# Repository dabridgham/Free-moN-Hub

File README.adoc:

= Free-monN Hub

This is a simple circuit board that acts as a wiring hub for a
Free-moN module or section.  It basically just replaces (some of) the
terminal strips that one might use on a simple module and adds a 12
VDC linear regulator, a reversing relay, and LEDs to indicate power on
the ACC and DCC busses.

See the https://github.com/dabridgham/Free-moN-Hub/wiki[wiki] for more
information.

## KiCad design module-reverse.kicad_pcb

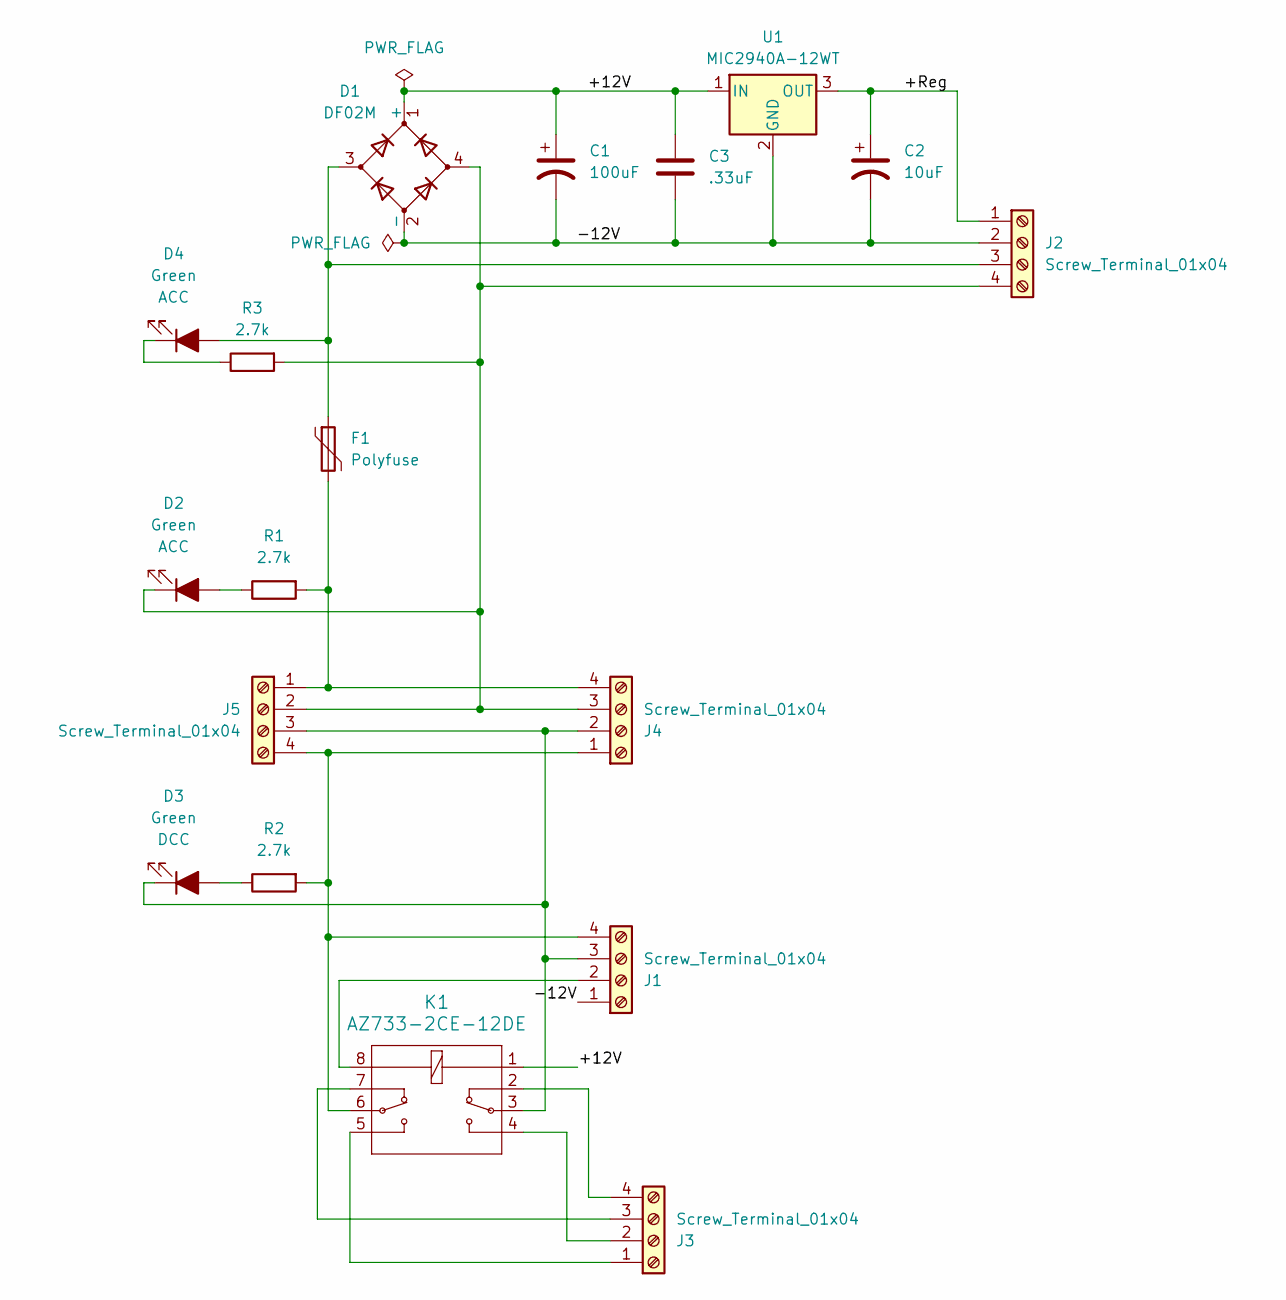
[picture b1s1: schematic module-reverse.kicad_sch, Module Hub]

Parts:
C1: 100uF; CP_Radial_D8.0mm_P3.50mm; MPN 50YXJ100MT78X11.5
C2: 10uF; CP_Radial_Tantal_D5.5mm_P5.00mm; MPN TAP106K025CRS
C3: .33uF; C_Disc_D5.0mm_W2.5mm_P5.00mm; MPN FA24X7R1H334KNU06
D1: DF02M; Diode_Bridge_DIP-4_W7.62mm_P5.08mm; MPN DF02M
D2, D3, D4: Green; LED_D3.0mm; MPN 151031VS06000
F1: Polyfuse; Fuse_Bourns_MF-RG300; MPN MF-R020
J1, J2, J3, J4, J5: Screw_Terminal_01x04; CUI_TB005-762-04BE; MPN TB005-762-04BE
K1: AZ733-2CE-12DE; AZ733-2C_AMZ; MPN AZ733-2CE-12DE
R1, R2, R3: 2.7k; R_Axial_DIN0207_L6.3mm_D2.5mm_P10.16mm_Horizontal; MPN CFR-25JB-52-2K7
U1: MIC2940A-12WT; TO-220-3_Vertical; MPN MIC2940A-12WT

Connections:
/+12V: C1.1, C3.1, D1.1 (+), K1.1, U1.1 (IN)
/+Reg: C2.1, J2.1, U1.3 (OUT)
/-12V: C1.2, C2.2, C3.2, D1.2 (-), J1.1, J2.2, U1.2 (GND)
unnamed: D2.2 (A), R1.1
unnamed: D1.4, D2.1 (K), J2.4, J4.3, J5.2, R3.2
unnamed: D3.2 (A), R2.1
unnamed: D3.1 (K), J1.3, J4.2, J5.3, K1.3
unnamed: D1.3, D4.2 (A), F1.1, J2.3
unnamed: D4.1 (K), R3.1
unnamed: J1.2, K1.8
unnamed: J1.4, J4.1, J5.4, K1.6, R2.2
unnamed: J3.1, K1.5
unnamed: J3.2, K1.4
unnamed: J3.3, K1.7
unnamed: J3.4, K1.2
unnamed: F1.2, J4.4, J5.1, R1.2

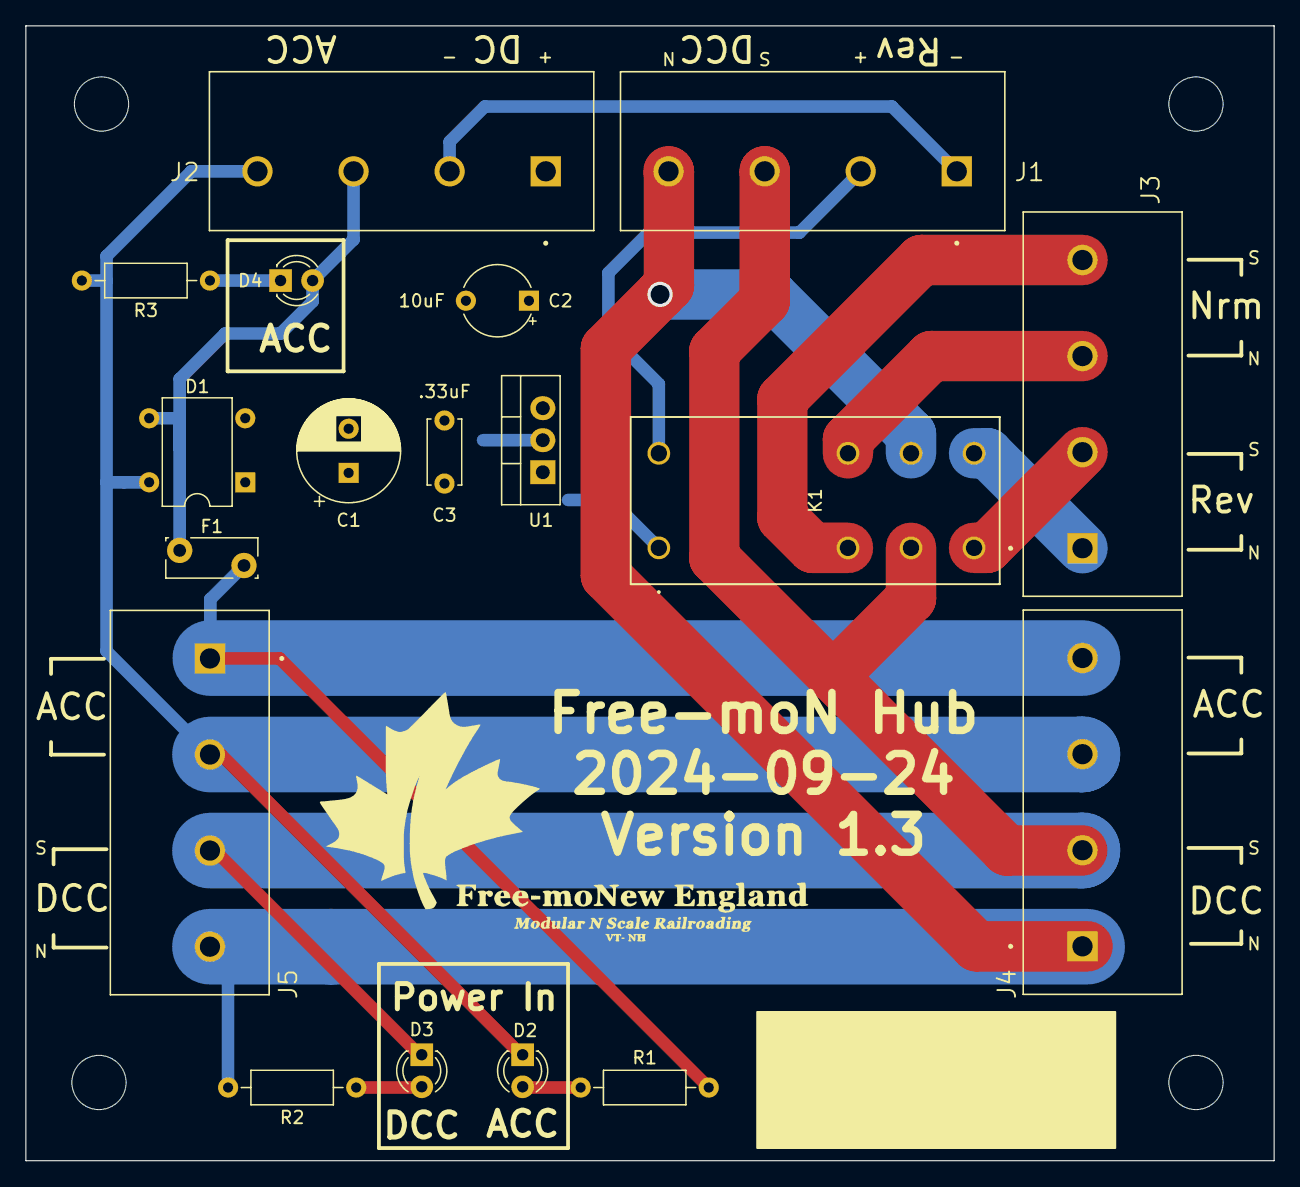
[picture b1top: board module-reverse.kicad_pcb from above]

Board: 2 copper layers, 99.0 x 90.0 mm, 18 parts (0 on the bottom side), 16 nets.

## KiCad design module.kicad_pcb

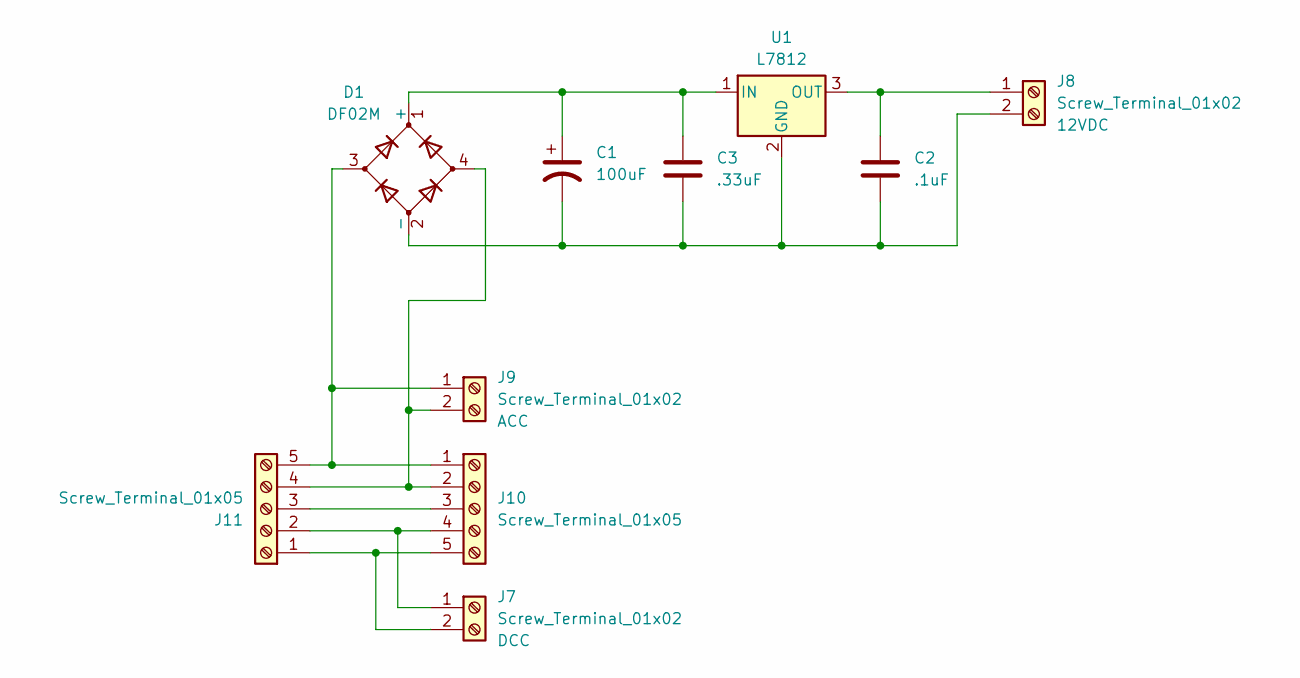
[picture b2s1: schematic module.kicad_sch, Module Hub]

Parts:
C1: 100uF; CP_Radial_D8.0mm_P3.50mm; MPN 50YXJ100MT78X11.5
C2: .1uF; C_Disc_D5.0mm_W2.5mm_P5.00mm; MPN FA28X7R1H104KNU00
C3: .33uF; C_Disc_D5.0mm_W2.5mm_P5.00mm; MPN FA24X7R1H334KNU06
D1: DF02M; Diode_Bridge_DIP-4_W7.62mm_P5.08mm; MPN DF02M
J7, J8, J9: Screw_Terminal_01x02; CUI_TB005-762-02BE; MPN TB005-762-02BE
J10, J11: Screw_Terminal_01x05; CUI_TB005-762-05BE; MPN TB005-762-05BE
U1: L7812; TO-220-3_Vertical; MPN L7812CV

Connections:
unnamed: C1.1, C3.1, D1.1 (+), U1.1 (IN)
unnamed: C1.2, C2.2, C3.2, D1.2 (-), J8.2, U1.2 (GND)
unnamed: C2.1, J8.1, U1.3 (OUT)
unnamed: D1.3, J9.1, J10.1, J11.5
unnamed: D1.4, J9.2, J10.2, J11.4
unnamed: J10.3, J11.3
unnamed: J7.1, J10.4, J11.2
unnamed: J7.2, J10.5, J11.1

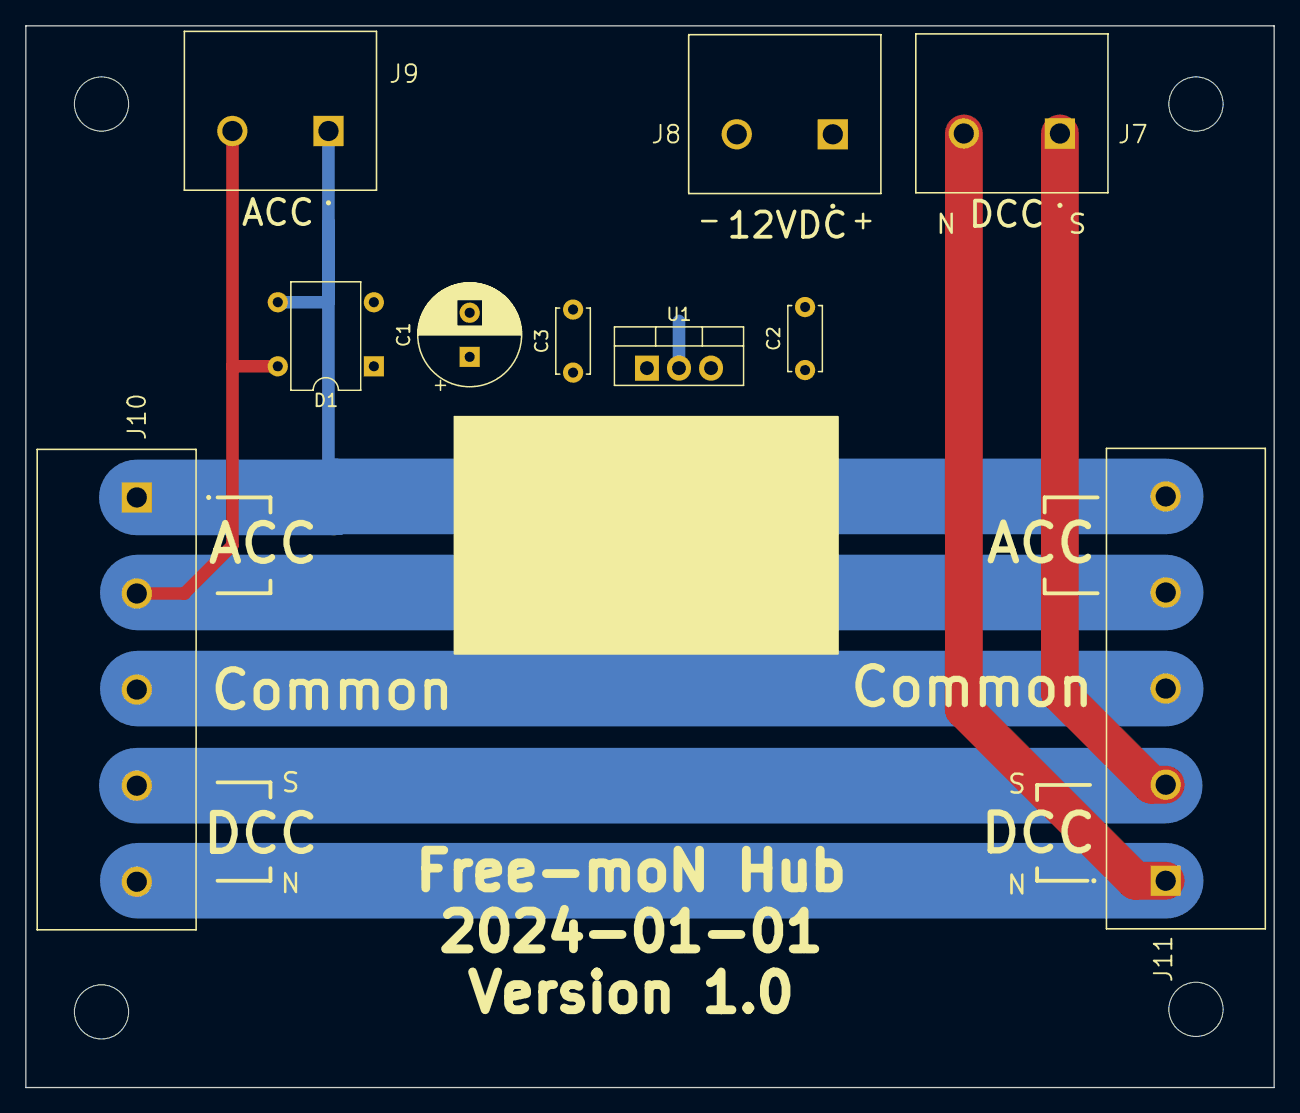
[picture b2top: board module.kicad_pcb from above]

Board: 2 copper layers, 99.0 x 84.2 mm, 10 parts (0 on the bottom side), 8 nets.

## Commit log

2024-01-01 Initial version and first boards.
2024-01-01 Generated fabrication files for v1.0
2024-01-01 Added the +/- and N/S indications to the silk layer
2024-01-01 Corrected spelling of Free-moN
2024-01-03 Added reversing relay and changed lower current screw terminals to a smaller style.
2024-01-03 Needed to actually add the files with their names changed.
2024-01-04 Changed the reversing output to have both Normal and Reverse outputs that go to the two branches instead of a single output that reverses.
2024-02-23 Added LEDs
2024-03-01 Updated reelase date and produced files for v1.1
2024-03-01 Forgot to save the file before committing in git. Now the date is updated
2024-04-09 Moved power to relay to before the voltage regulator
2024-06-14 Updated to KiCad v8
2024-06-14 Initial README, just copied from
2024-06-14 Initial README.adoc
2024-09-24 Added a PTC fuse to the ACC power and an additional LED to show its status
2025-02-09 Updated LEDs
2025-06-10 Removed the comment that the Wiki was not yet written
2025-06-10 Updated to KiCad 9.0
